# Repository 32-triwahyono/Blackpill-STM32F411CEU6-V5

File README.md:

# Blackpill STM32F411CEU6 V5 Baseboard Design

## 📌 Deskripsi Proyek
Desain modul/baseboard PCB untuk mikrokontroler STM32F411CEU6 (Blackpill Core Board) menggunakan **KiCad**. Proyek ini mencakup perancangan skematik, tata letak jalur PCB 2-layer, serta pembuatan berkas manufaktur (Gerber).

## 🛠️ Spesifikasi Hardware & PCB
- **Microcontroller:** STM32F411CEU6 (ARM Cortex-M4 32-bit)
- **PCB Layers:** 2-Layer Board (Top & Bottom Ground Plane)
- **Substrat & Ketebalan:** FR-4, 1.6 mm, 1 oz Copper
- **Antarmuka & Port:** Header ekspresi GPIO, Port SWD Debug, Power Indicator LED
- **Desain software:** KiCad EDA

## 📁 Struktur Repositori
- `*.kicad_sch` : Berkas skematik elektronik
- `*.kicad_pcb` : Berkas tata letak (layout) PCB
- `*.kicad_pro` : Berkas proyek utama KiCad
- `gerber.zip`   : Berkas manufaktur siap cetak (JLCPCB / PCBWay)

## 📸 Skematik & Layout PCB

## 🚀 Pengujian & Manufaktur
- [x] Design Rules Check (DRC) KiCad: **0 Errors / 0 Warnings**
- [x] Berkas Gerber & Drill file terverifikasi di Gerber Viewer

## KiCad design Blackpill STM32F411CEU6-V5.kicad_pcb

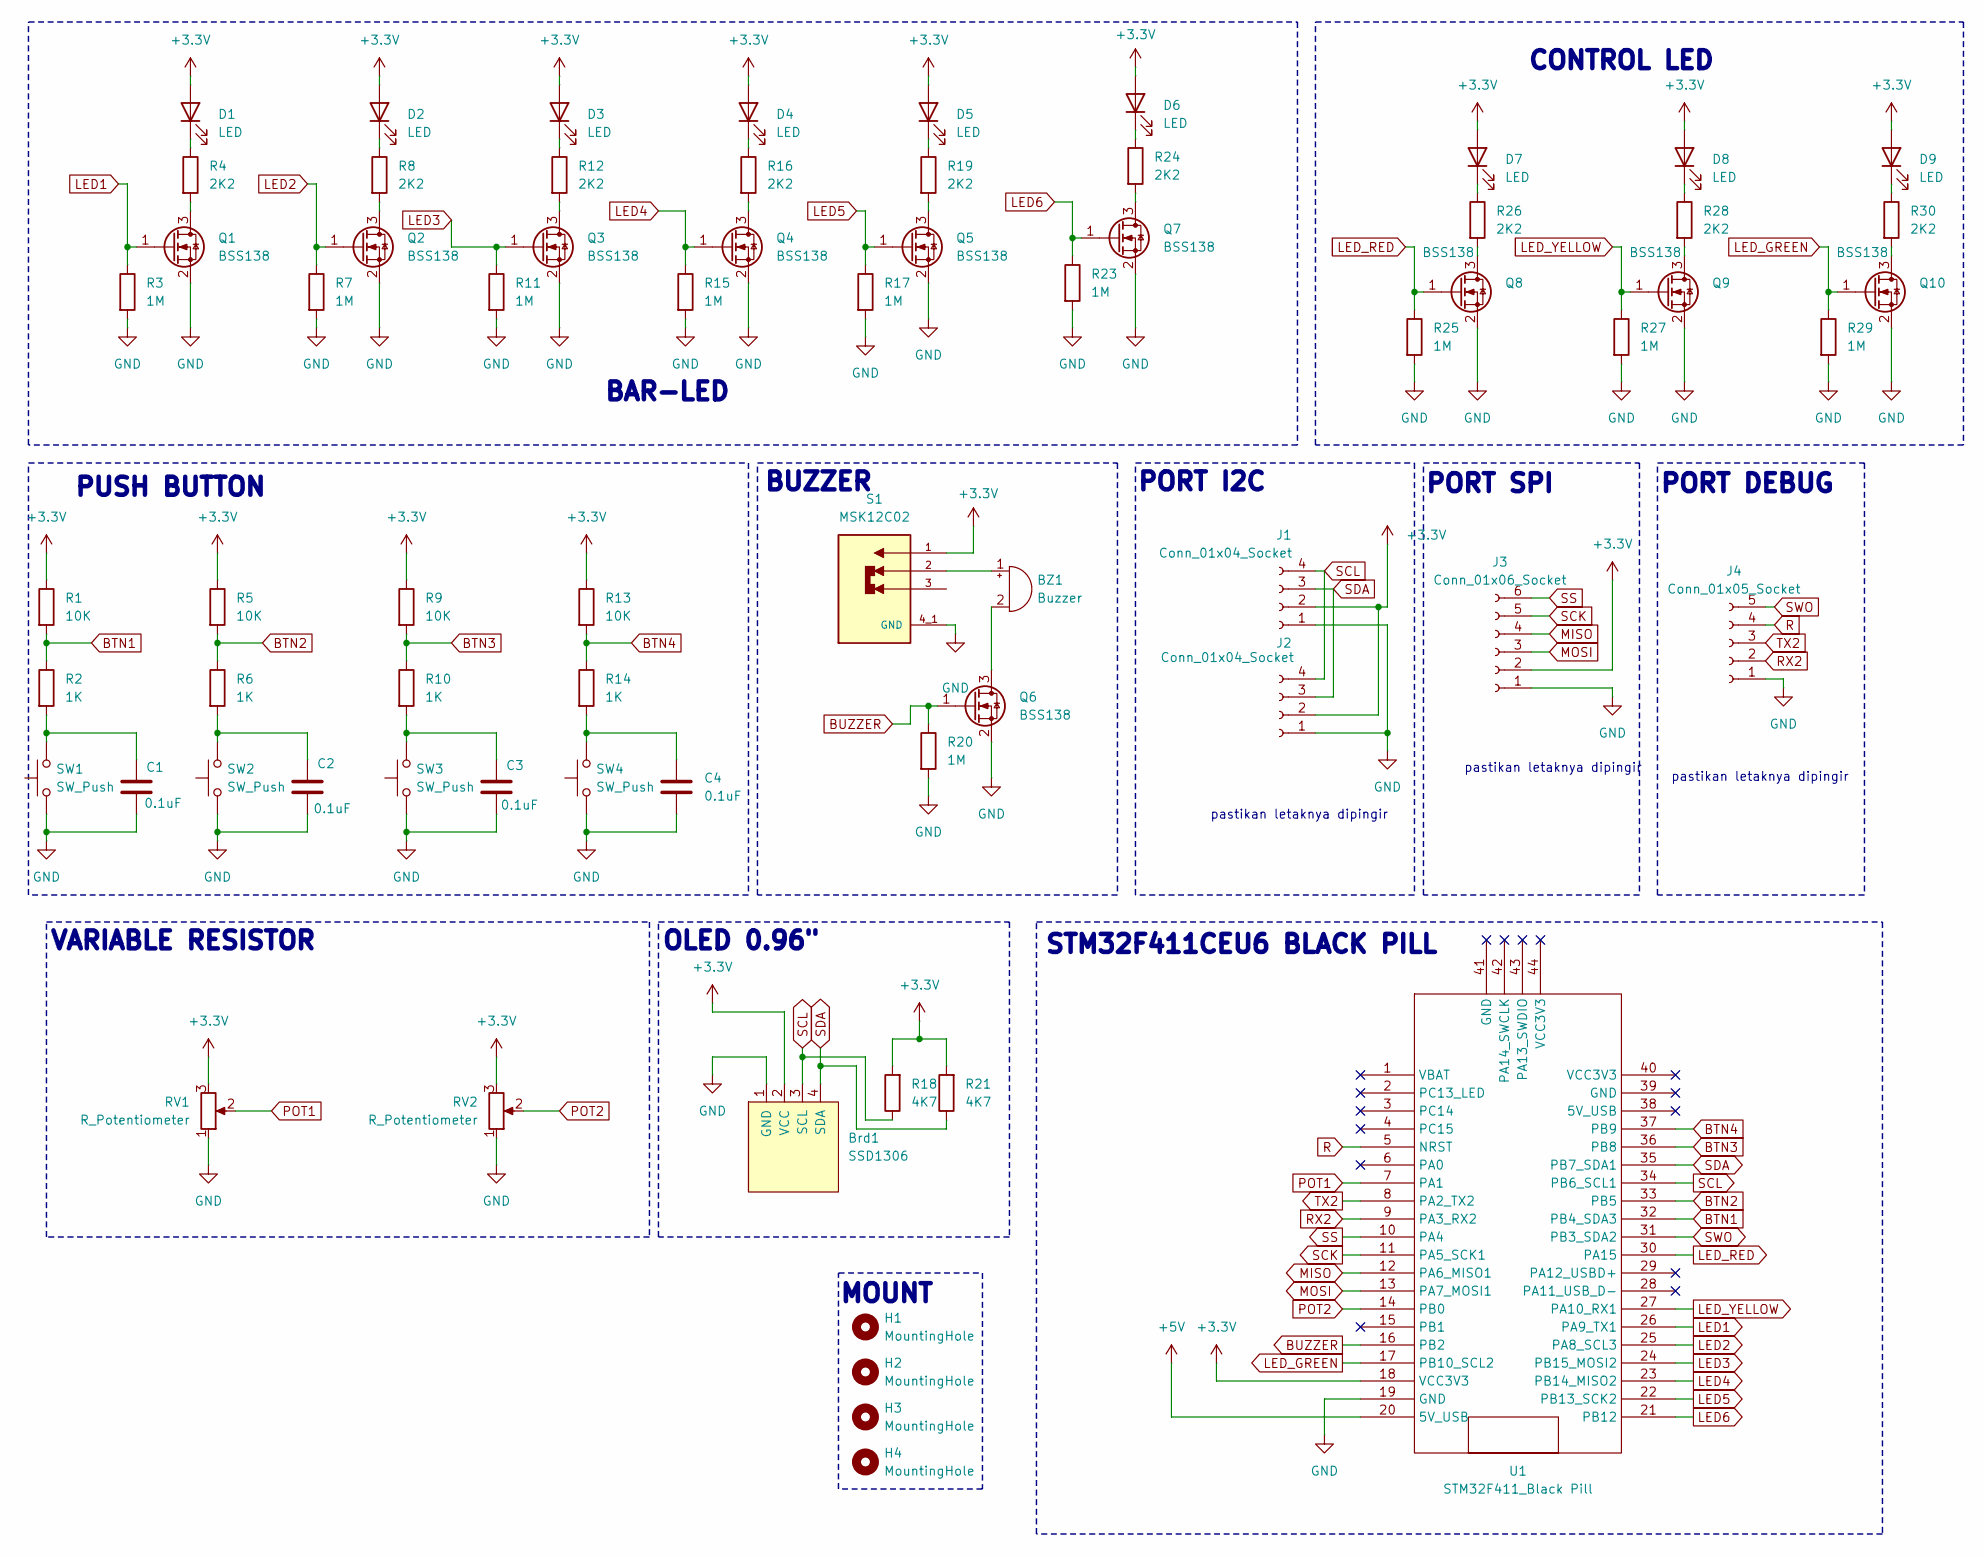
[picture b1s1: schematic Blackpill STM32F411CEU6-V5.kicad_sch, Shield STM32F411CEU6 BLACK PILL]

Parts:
BZ1: Buzzer; Buzzer_12x9.5RM7.6
Brd1: SSD1306; 128x64OLED
C1, C2, C3, C4: 0.1uF; C_0805_2012Metric_Pad1.18x1.45mm_HandSolder
D1, D2, D3, D4, D5, D6, D7, D8, D9: LED; LED_0805_2012Metric_Pad1.15x1.40mm_HandSolder
H1, H2, H3, H4: MountingHole; MountingHole_3.2mm_M3
J1, J2: Conn_01x04_Socket; JST_PH_B4B-PH-K_1x04_P2.00mm_Vertical
J3: Conn_01x06_Socket; JST_PH_B6B-PH-K_1x06_P2.00mm_Vertical
J4: Conn_01x05_Socket; PinSocket_1x05_P2.54mm_Vertical
Q1, Q2, Q3, Q4, Q5, Q6, Q7, Q8, Q9, Q10: BSS138; SOT-23_Handsoldering
R1, R5, R9, R13: 10K; R_0805_2012Metric_Pad1.20x1.40mm_HandSolder
R2, R6, R10, R14: 1K; R_0805_2012Metric_Pad1.20x1.40mm_HandSolder
R3, R7, R11, R15, R17, R20, R23, R25, R27, R29: 1M; R_0805_2012Metric_Pad1.20x1.40mm_HandSolder
R4, R8, R12, R16, R19, R24, R26, R28, R30: 2K2; R_0805_2012Metric_Pad1.20x1.40mm_HandSolder
R18, R21: 4K7; R_0603_1608Metric
RV1, RV2: R_Potentiometer; Potentiometer_Bourns_3386P_V
S1: MSK12C02; SW_MSK12C02; PARTREV A/0
SW1, SW2, SW3, SW4: SW_Push; SW_PUSH_6mm
U1: STM32F411_Black Pill

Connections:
+3.3V: Brd1.2 (VCC), D1.2 (A), D2.2 (A), D3.2 (A), D4.2 (A), D5.2 (A), D6.2 (A), D7.2 (A), D8.2 (A), D9.2 (A), J1.2, J2.2, J3.2, R1.1, R5.1, R9.1, R13.1, R18.2, R21.2, RV1.3, RV2.3, S1.1, U1.18 (VCC3V3)
+5V: U1.20 (5V_USB)
BTN1: R1.2, R2.1, U1.32 (PB4_SDA3)
BTN2: R5.2, R6.1, U1.33 (PB5)
BTN3: R9.2, R10.1, U1.36 (PB8)
BTN4: R13.2, R14.1, U1.37 (PB9)
BUZZER: Q6.1 (G), R20.1, U1.16 (PB2)
GND: Brd1.1 (GND), C1.2, C2.2, C3.2, C4.2, J1.1, J2.1, J3.1, J4.1, Q1.2 (S), Q2.2 (S), Q3.2 (S), Q4.2 (S), Q5.2 (S), Q6.2 (S), Q7.2 (S), Q8.2 (S), Q9.2 (S), Q10.2 (S), R3.2, R7.2, R11.2, R15.2, R17.2, R20.2, R23.2, R25.2, R27.2, R29.2, RV1.1, RV2.1, S1.4_1 (GND), S1.4_2 (GND), S1.4_3 (GND), S1.4_4 (GND), SW1.1, SW2.1, SW3.1, SW4.1, U1.19 (GND)
LED1: Q1.1 (G), R3.1, U1.26 (PA9_TX1)
LED2: Q2.1 (G), R7.1, U1.25 (PA8_SCL3)
LED3: Q3.1 (G), R11.1, U1.24 (PB15_MOSI2)
LED4: Q4.1 (G), R15.1, U1.23 (PB14_MISO2)
LED5: Q5.1 (G), R17.1, U1.22 (PB13_SCK2)
LED6: Q7.1 (G), R23.1, U1.21 (PB12)
LED_GREEN: Q10.1 (G), R29.1, U1.17 (PB10_SCL2)
LED_RED: Q8.1 (G), R25.1, U1.30 (PA15)
LED_YELLOW: Q9.1 (G), R27.1, U1.27 (PA10_RX1)
MISO: J3.4, U1.12 (PA6_MISO1)
MOSI: J3.3, U1.13 (PA7_MOSI1)
unnamed: BZ1.1 (+), S1.2
unnamed: BZ1.2 (-), Q6.3 (D)
unnamed: C1.1, R2.2, SW1.2
unnamed: C2.1, R6.2, SW2.2
unnamed: C3.1, R10.2, SW3.2
unnamed: C4.1, R14.2, SW4.2
unnamed: D1.1 (K), R4.1
unnamed: D2.1 (K), R8.1
unnamed: D3.1 (K), R12.1
unnamed: D4.1 (K), R16.1
unnamed: D5.1 (K), R19.1
unnamed: D6.1 (K), R24.1
unnamed: D7.1 (K), R26.1
unnamed: D8.1 (K), R28.1
unnamed: D9.1 (K), R30.1
unnamed: Q1.3 (D), R4.2
unnamed: Q2.3 (D), R8.2
unnamed: Q3.3 (D), R12.2
unnamed: Q4.3 (D), R16.2
unnamed: Q5.3 (D), R19.2
unnamed: Q7.3 (D), R24.2
unnamed: Q8.3 (D), R26.2
unnamed: Q9.3 (D), R28.2
unnamed: Q10.3 (D), R30.2
POT1: RV1.2, U1.7 (PA1)
POT2: RV2.2, U1.14 (PB0)
R: J4.4, U1.5 (NRST)
RX2: J4.2, U1.9 (PA3_RX2)
SCK: J3.5, U1.11 (PA5_SCK1)
SCL: Brd1.3 (SCL), J1.4, J2.4, R18.1, U1.34 (PB6_SCL1)
SDA: Brd1.4 (SDA), J1.3, J2.3, R21.1, U1.35 (PB7_SDA1)
SS: J3.6, U1.10 (PA4)
SWO: J4.5, U1.31 (PB3_SDA2)
TX2: J4.3, U1.8 (PA2_TX2)

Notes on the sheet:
pastikan letaknya dipingir
PORT DEBUG
PUSH BUTTON
PORT SPI
PORT I2C
OLED 0.96"
BUZZER
MOUNT
VARIABLE RESISTOR
CONTROL LED
BAR-LED
STM32F411CEU6 BLACK PILL

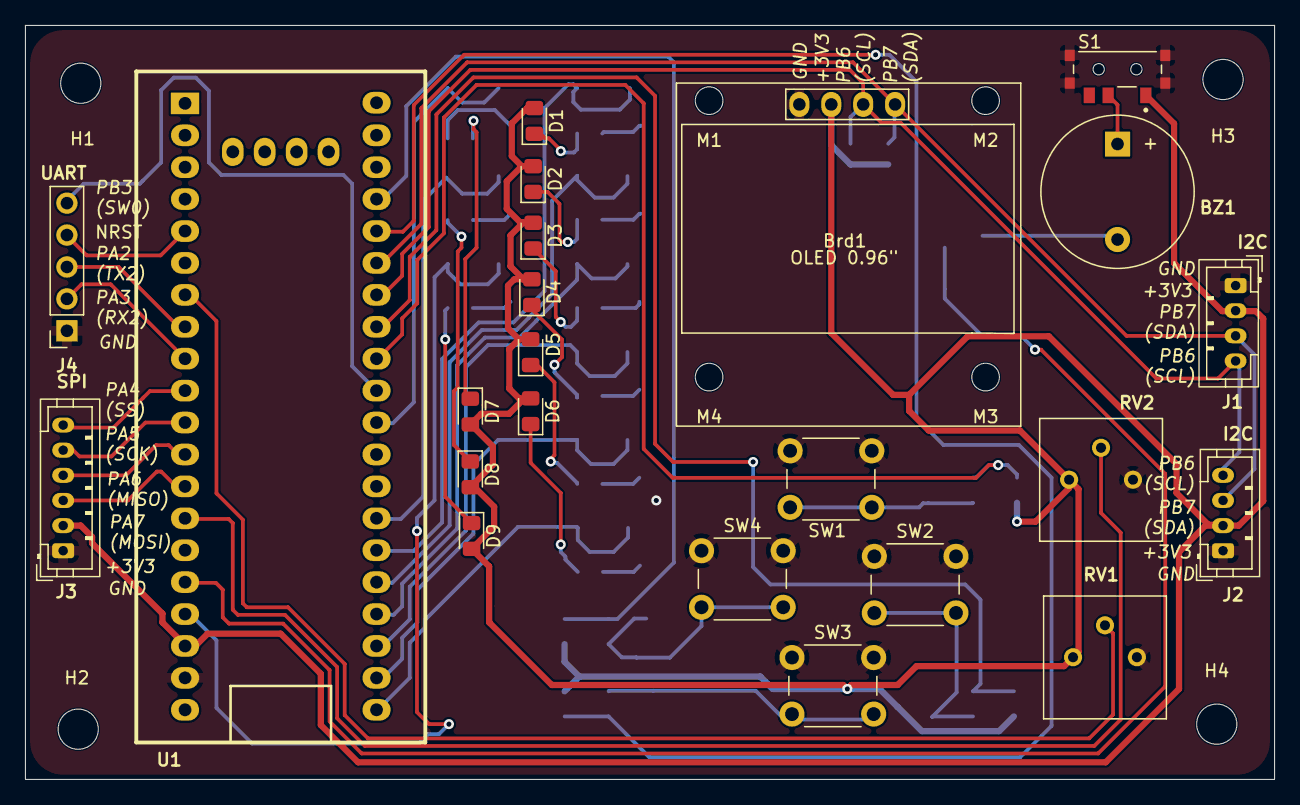
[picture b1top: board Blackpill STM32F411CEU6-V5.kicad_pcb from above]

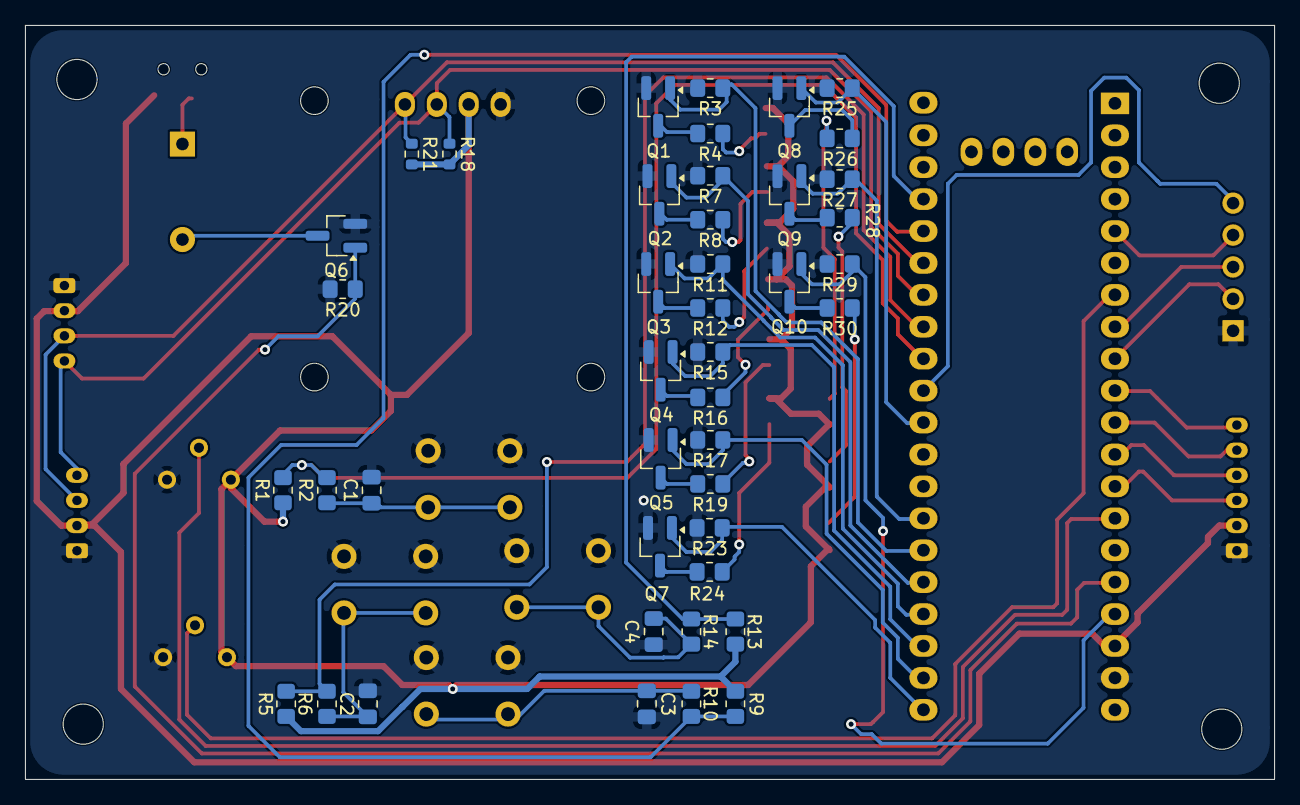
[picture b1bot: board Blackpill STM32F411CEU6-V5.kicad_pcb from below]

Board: 2 copper layers, 99.4 x 60.0 mm, 74 parts (43 on the bottom side), 52 nets.

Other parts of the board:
M1: M1; MountingHole_2.2mm_M2
M2, M3: M2; MountingHole_2.2mm_M2
M4: M4; MountingHole_2.2mm_M2
